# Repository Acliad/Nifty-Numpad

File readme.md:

Nifty Numpad is a full sized numpad with an extra row and two extra columns of macro keys. It was created because I wanted a companion to my TKL keyboard for work. My main workflow involves heavy use of ECAD programs, so the design was tailored for that, but it is generic enough to be nice for many workflows! 

The main features are:
- Full sized numpad with row of macro/function keys on the top
- Two extra columns of macro keys
- Cherry MX style socketed switches
- Backlit keys
- 3D printable case (FDM or resin)

.png "Render of Nifty Numpad")

# Contents
- [Contents](#contents)
- [Building One](#building-one)
  - [1. PCB Assembly](#1-pcb-assembly)
  - [2. 3D Printed Case](#2-3d-printed-case)
  - [3. Switch Mounting Plate](#3-switch-mounting-plate)
  - [4. Switches/Keycaps](#4-switcheskeycaps)
  - [5. Software](#5-software)
- [TODO](#todo)
  - [Software](#software)
- [Changelog](#changelog)
  - [PCB](#pcb)
    - [Rev 1](#rev-1)
  - [Software](#software-1)
  - [Mechanical](#mechanical)

# Building One
All of the files needed to build this numpad are in this repo (with software as a submodule and in the main QMK repo). The total BOM cost will be somewhere around $65-$85 shipped, but depends heavily on where and how you source things like switches, keycaps, plate, etc. For example, I bought 120x switches, but if you could get 33 switches for cheaper, you might save ~$10. 

## 1. PCB Assembly
The most difficult part of the build is soldering the RP2040 (microcontroller used) and associated components. It is highly recommended that you have the PCBs assembled. The files are in this repo for getting the PCB assembled through JLC PCB. You may save some money by soldering some of the components yourself (especially the sockets and LEDs). However, if you just love to solder this can be done with a stencil and plenty of time. I should know 🥲

You can choose to omit the LEDs if you're not into that sort of thing. It'll save you a few bucks. 

Parts marked as (DNF) in the BOM are not meant to be populated. If you want easy debugging for software development, you can populate R103, SW101, and SW102.

To have the PCB assembled:
1. Upload the gerber files from PCB/Main PCB/production/Nifty_Numpad.zip to JLC PCB.
2. Check the PCB Assembly toggle on the JLC PCB order page.
   1. Choose the PCBA Type. If you want JLC to solder the LEDs and sockets for you, you need to choose Standard. Otherwise, choose economy. Economy is a bit cheaper.
3. On the PCB Assembly page, you will need to upload the bom.csv and positions.csv file from PCB/Main PCB/production/
4. On the Components Placements page, make sure all of the ICs are orientated correctly. They usually aren't by default since JLC's library orientation is generally different from KiCad's.

To Solder the PCB assembly yourself:
1. Order PCBs (I use JLC, you can use whomever you like).
2. Order a stencil (you can usually do this at the same time as the PCB).
3. Order parts (I have DigiKey PNs in the electrical BOM, but again feel free to substitute)
   - The switch sockets are not available on DigiKey. [I bought mine on Amazon](https://www.amazon.com/dp/B0BVH6M5FP?psc=1&ref=ppx_yo2ov_dt_b_product_details), but you can source them from most keyboard suppliers.
   - The LEDs come in packs of 10. You can get them from DigiKey or Adafruit, but note if you upload the BOM directly to DigiKey it will put in a quantity of 33, which is actually 330.
4. Solder it!
    - I recommend a reflow oven, but a hot air station or hot plate works too.

## 2. 3D Printed Case
This case was initially designed to be 3D printed on a resin printer, but it actually prints best on an FDM printer. There are not special instructions here. You can either print the case yourself or have it printed using a service. JLC offers printing of many varieties. This might be a good choice if you're already ordering the PCB from them.

All the screw holes are designed to be tapped by a self-tapping screw. The BOM has some recommendations for some plastic-threading screws. 

I have added a "[shadow line](https://www.youtube.com/watch?v=8dhFhU7Nl_0)" to the case outline. There's a top-case print option with and without this line. I think it helps the look a bit for FDM prints, but it's up to you. 

It helps the sound profile considerably to fill up the case with some kind of dampening material. You could use foam or pour castable silicone into the case (I used [this one](https://www.amazon.com/gp/product/B07V5FFPWC/ref=ppx_yo_dt_b_search_asin_title?ie=UTF8&psc=1)). You can (and probably should) pour the silicone directly into the case. However, I've also included a mold for this in the Mechanical folder.

## 3. Switch Mounting Plate
I used [plate-mount](https://switchandclick.com/plate-mounted-vs-pcb-mounted-keyboard/) switches on this design. You can either make your own plate or have one made for you. There's a model of the plate as well as a DXF file in the Mechanical folder. Here is some information about some options:

1. Order a plate out of FR-4 when you order the PCB
   - This is a good option if you're already ordering the PCB from JLC. You can order the plate at the same time and save on shipping. 
   - This plate is quite rigid and I've found it to work well.
2. Order or make a custom plate out of your preferred material.
    - If you have a laser cutter or CNC, you can use the DXF or step file to make a plate out of whatever material you like! Many people use plexilgass, but you could use wood or metal. 
3. Use the provided 3D model of the plate to 3D print a plate.
   - The plate works, but it's quite flimsy and makes taking all the switches off the PCB tedious

Whatever you choose to do, you should find appropriate files in the Mechanical folder.

## 4. Switches/Keycaps
The fun part! Choose your favorite Cherry MX compatible switches and pop them in. If you're using LEDs, make sure you get switches with a clear top. 

I found it difficult to source backlit keycaps that fit this build well. You might be better off using non-backlit keycaps. There are [some AliExpress sellers](https://www.aliexpress.us/item/3256801609324454.html?spm=a2g0o.order_list.order_list_main.18.27561802CbfaCa&gatewayAdapt=glo2usa) who will sell portions of a keyboard at a time so you can mix and match colors. This is what I ended up doing, but I couldn't find any in a uniform profile like XDA or DSA. If you find a good source of keycaps, please share! 

If you're feeling plush, I think the numpad + icono kits of [these keycaps](https://drop.com/buy/drop-biip-mt3-extended-custom-keycap-set?mode%5B0%5D=shop_open&mode%5B1%5D=shop_open&defaultSelectionIds=969832&utm_source=google&utm_medium=cpc&utm_campaign=14650997430&utm_term=126026139486&utm_content=545898905914&utm_keyword=&utm_placement=pla-1392002507270&utm_network=u%3Ac%3A%3A&utm_device=&gad=1&gclid=CjwKCAjwlJimBhAsEiwA1hrp5i-AwICvpmNDm80DELJZylLo96oIX7IjxFvtUybMUVPNlUNpxAKwlxoCEOMQAvD_BwE&gclsrc=aw.ds) would be really nice. 

You'll also need 3x 2u plate-mount stabilizers. You can source these from most keyboard part suppliers or Ali Express.

## 5. Software
I've used [QMK](https://qmk.fm) for this build. Theere are builds for the [VIA](https://www.caniusevia.com) GUI configurator, a basic default usage, and an example for how to use the "fancy" RGB Idle mode and some tap-dance features. VIA is probably the easiest way to configure the keymap since you can configure it over a GUI, but if you're comfortable with QMK, you can do some cool customizations.

The Nifty Numpad has been merged into the main QMK repo, which you can find [here](https://github.com/qmk/qmk_firmware). My personal fork for developing the keyboard software is a submodule of this repo. You can find it [here](https://github.com/Acliad/qmk_firmware).

QMK and the build/flash process is pretty well document, so I'll leave that to the QMK community. If you have specific issues with the Nifty Numpad, feel free to message me. 

# TODO
## Software
- ~Implement VIAL for GUI remapping of buttons~
- ~Add other keymaps (an actual default and rename current to Cadence is a good start)~
- Create visual legend for RGB settings layer

# Changelog
## PCB
### Rev 1
- Changed footprint for W25Q40CLSNIG from wide to narrow footprint to match DigiKey PN
- Changed standoff holes to 6.0mm (from 4.6mm)
- Update LED footprint
- Add WASD graphic

## Software
- Added additional keymaps: default, VIA, and example. Old default moved to "Cadence" keymap
- Cleaned up code and file structure to align with QMK standards

## Mechanical
- Updated plate to use pan head screws
- Added clearance to top piece for pan head plate mount screws
- Moved "Designed By" tag to inside numpad
- Added a silicone sound dampening mold
- Added a "[shadow line](https://www.youtube.com/watch?v=8dhFhU7Nl_0)" model

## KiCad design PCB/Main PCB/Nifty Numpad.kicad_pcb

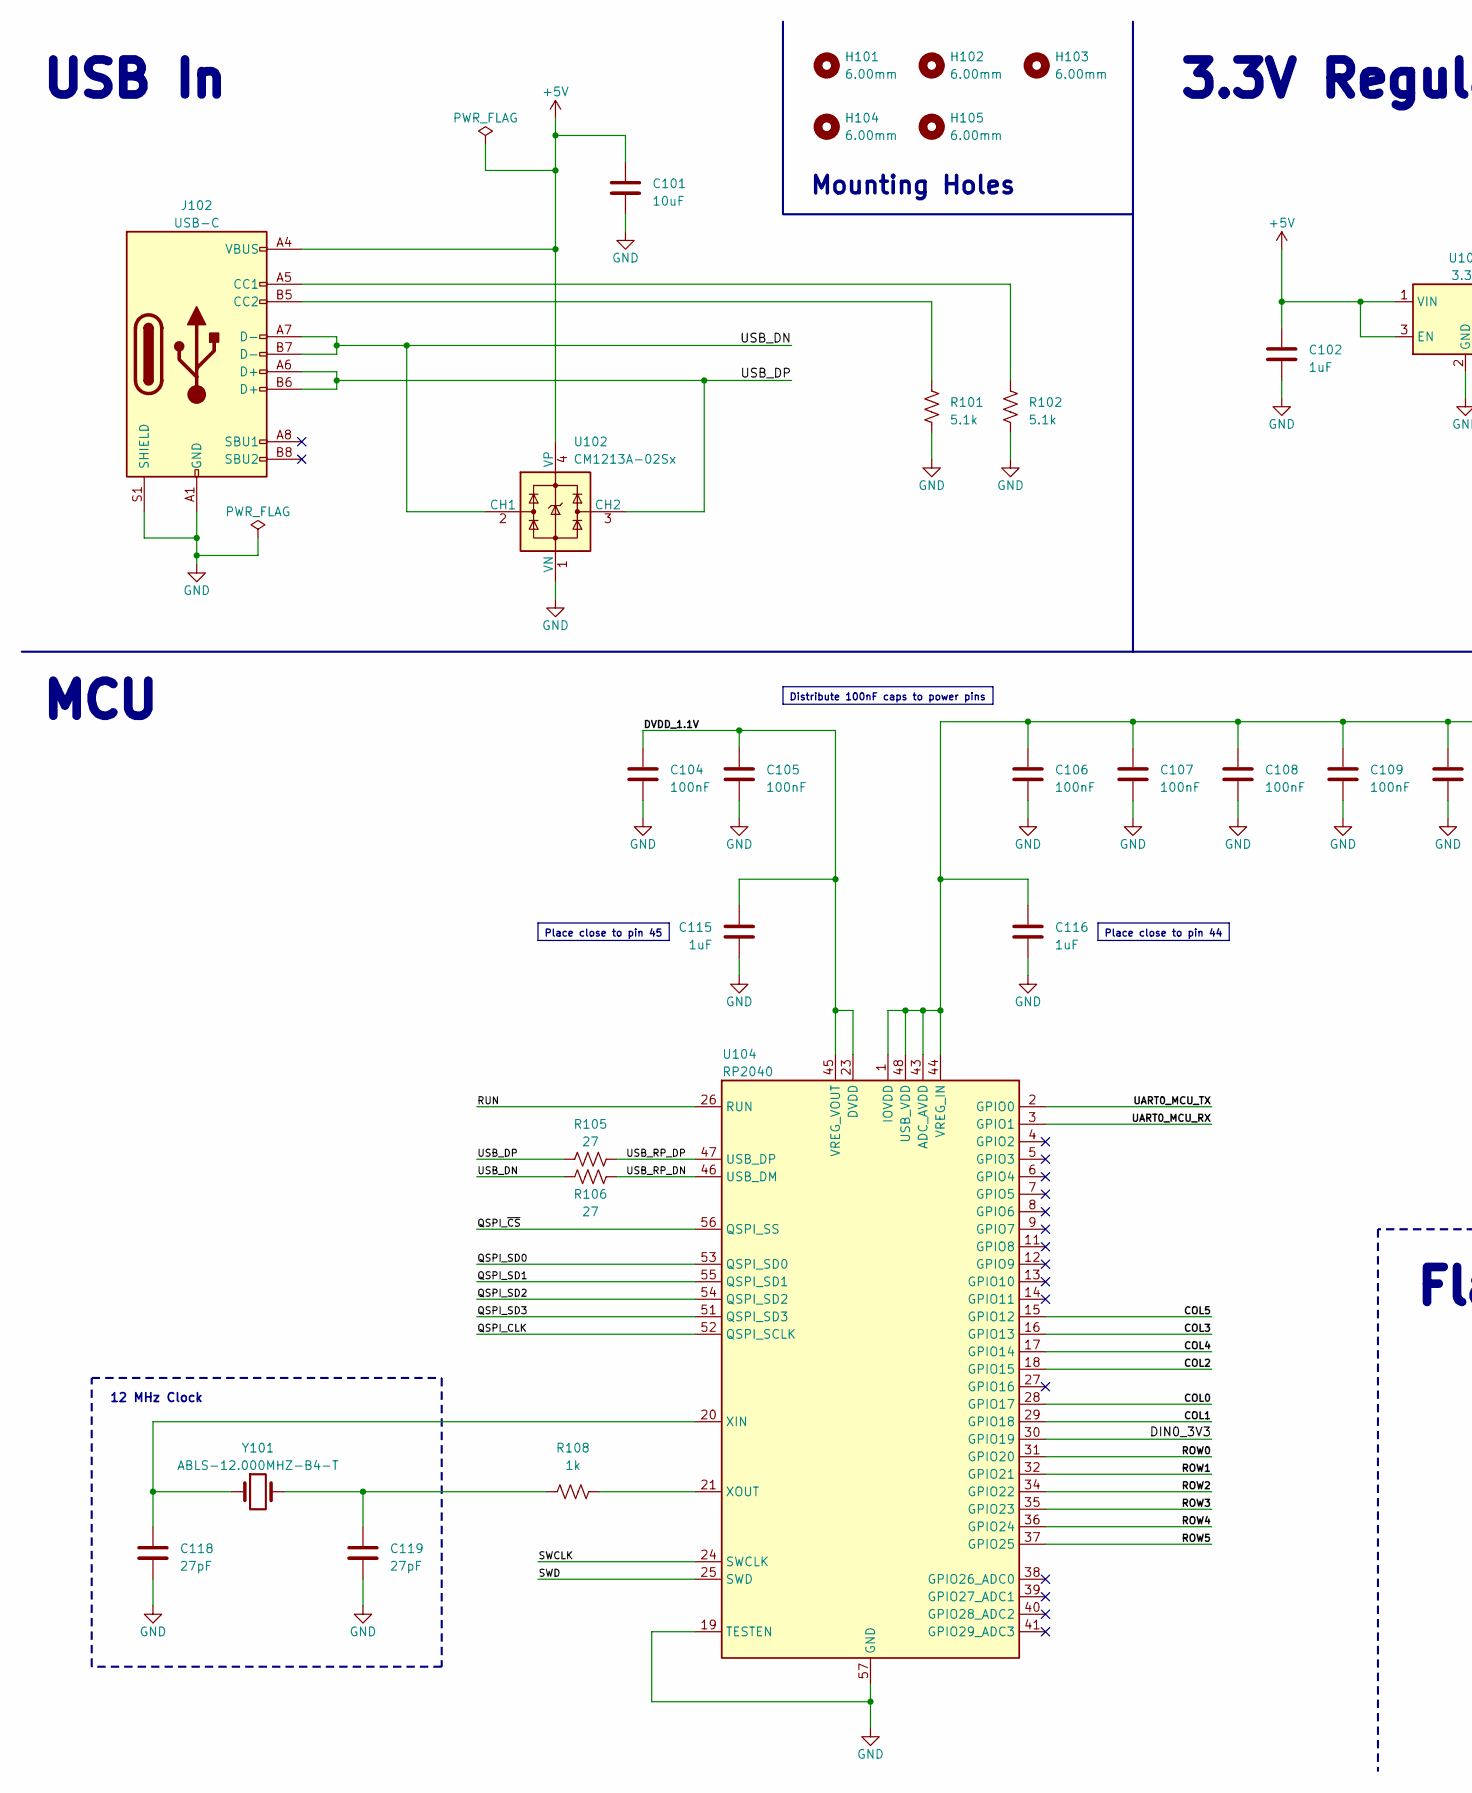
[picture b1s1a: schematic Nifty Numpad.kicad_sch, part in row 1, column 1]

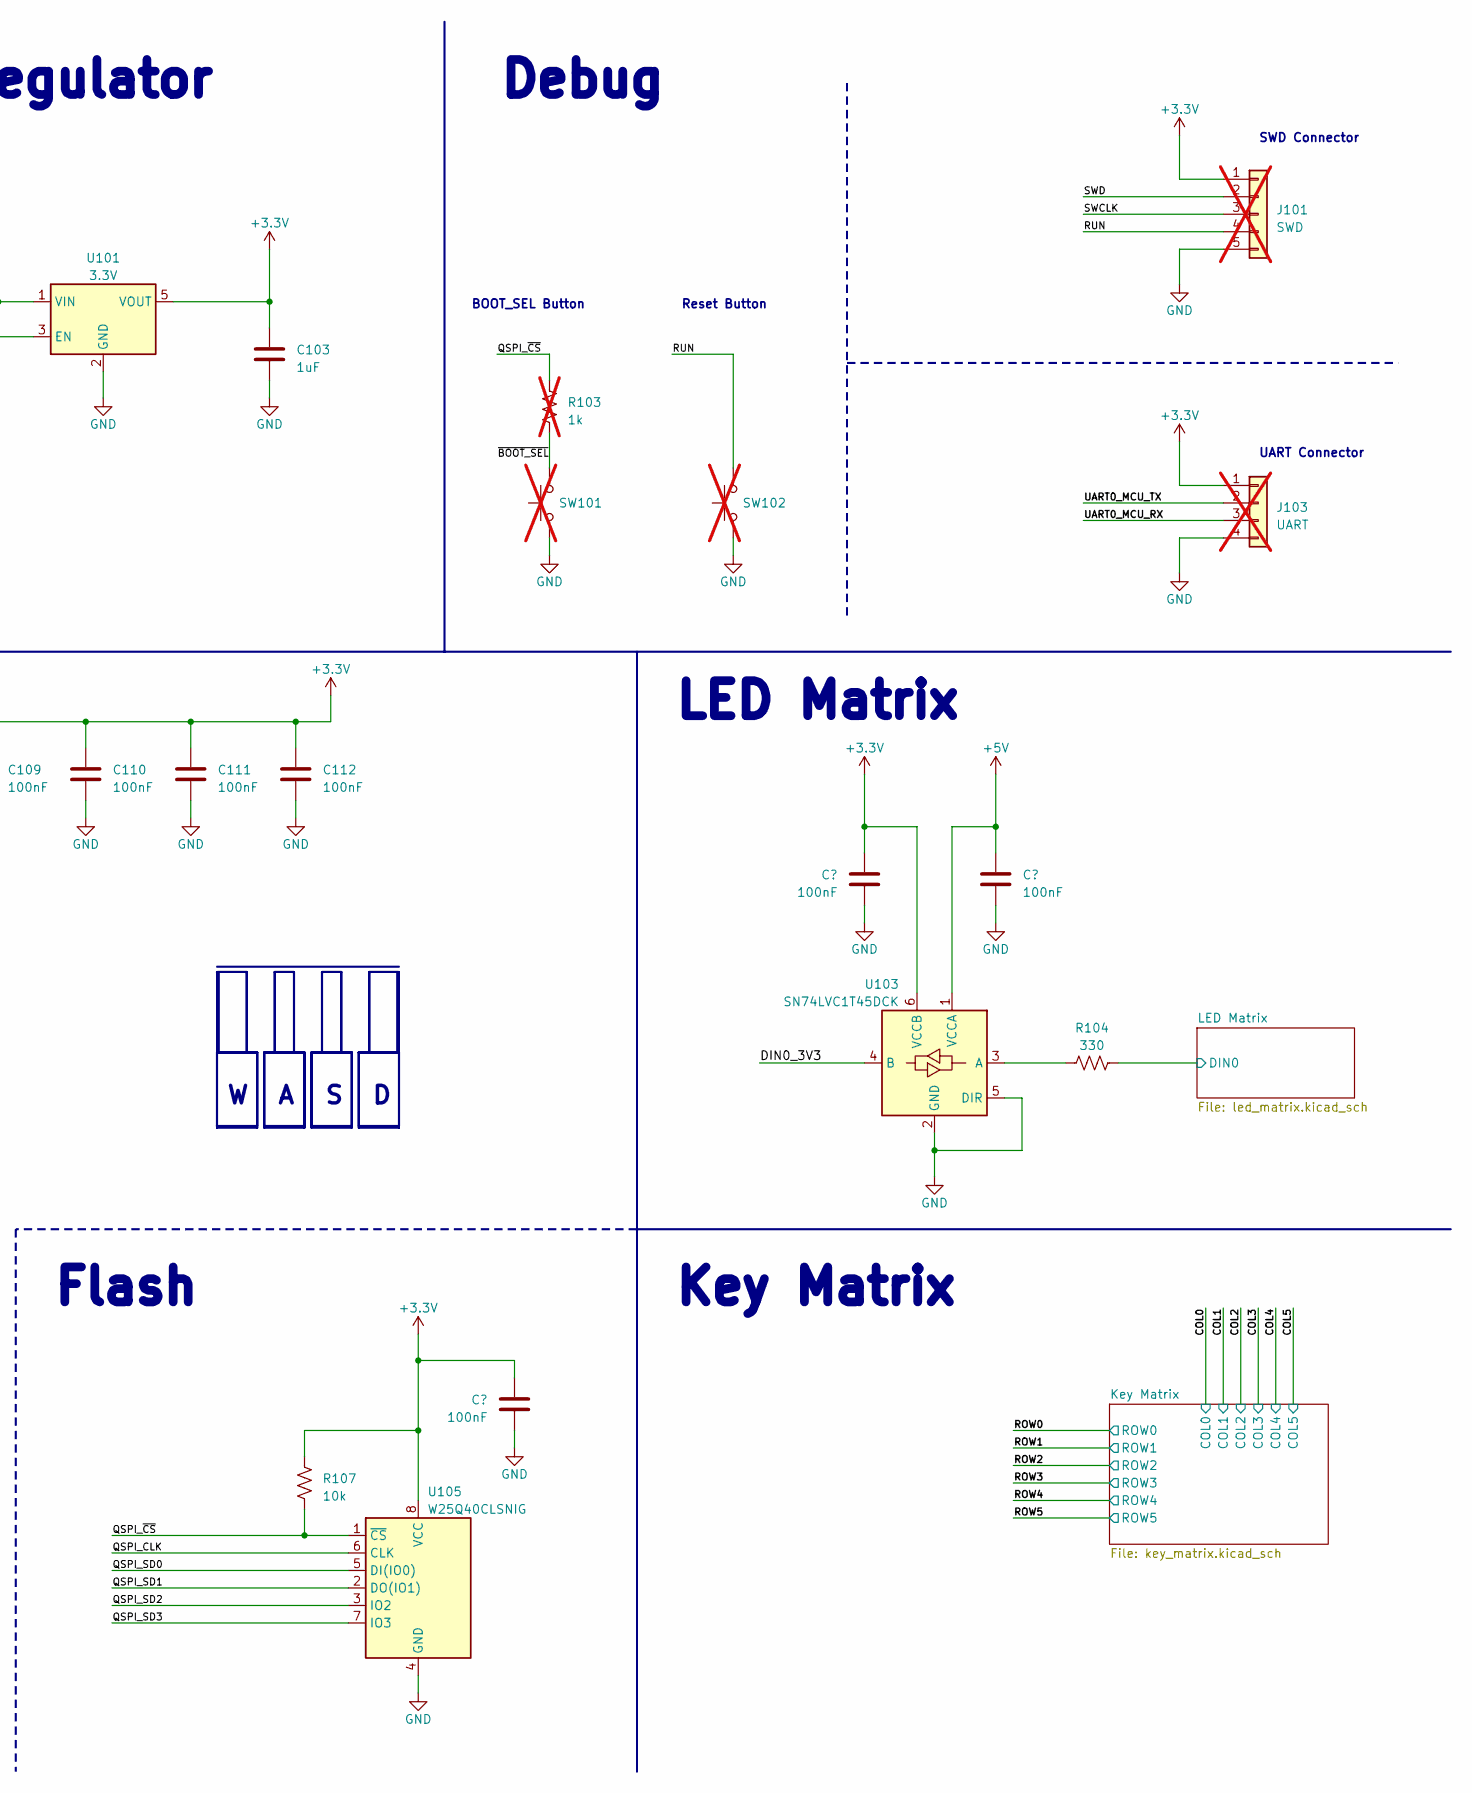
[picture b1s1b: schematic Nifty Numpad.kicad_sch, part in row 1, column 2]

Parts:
C101: 10uF; C_0603_1608Metric; DigiKey PN 490-10475-1-ND
C102, C103, C115, C116: 1uF; C_0603_1608Metric; DigiKey PN 1276-6524-1-ND
C104, C105, C106, C107, C108, C109, C110, C111, C112, C113, C114, C117: 100nF; C_0603_1608Metric; DigiKey PN 1276-1006-1-ND
C118, C119: 27pF; C_0603_1608Metric; DigiKey PN 1276-2247-1-ND
H101, H102, H103, H104, H105: 6.00mm; MountingHole_6.0mm_ReducedCourtyard
J101: SWD; PinHeader_1x05_P2.54mm_Vertical; DigiKey PN 2057-PH1-05-UA-ND; not fitted
J102: USB-C; USB_C_Receptacle_GCT_USB4105-GF-A-060; DigiKey PN 2073-USB4105-GF-A-060CT-ND
J103: UART; PinHeader_1x04_P2.54mm_Vertical; DigiKey PN 2057-PH1-04-UA-ND; not fitted
R101, R102: 5.1k; R_0603_1608Metric; DigiKey PN CR0603-FX-5101ELFCT-ND
R103: 1k; R_0603_1608Metric; DigiKey PN RNCP0603FTD1K00CT-ND; not fitted
R104: 330; R_0603_1608Metric; DigiKey PN CR0603-FX-3300ELFCT-ND
R105, R106: 27; R_0603_1608Metric; DigiKey PN CR0603-FX-27R0ELFCT-ND
R107: 10k; R_0603_1608Metric; DigiKey PN RNCP0603FTD1K00CT-ND
R108: 1k; R_0603_1608Metric; DigiKey PN RNCP0603FTD1K00CT-ND
SW101, SW102: PTS636 SL43 SMTR LFS; SW-PUSH-6x3.5mm_CK-PTS636SL43x_HandSolder; DigiKey PN CKN12309-1-ND; not fitted
U101: 3.3V; SOT-353_SC-70-5; DigiKey PN 576-3215-1-ND
U102: CM1213A−02Sx; SOT-143; DigiKey PN CM1213A-02SROSCT-ND
U103: SN74LVC1T45DCK; SOT-363_SC-70-6; DigiKey PN 31-74LVC1T45DW-7CT-ND
U104: RP2040; QFN-56-1EP_7x7mm_P0.4mm_EP3.2x3.2mm; DigiKey PN 2648-SC0914(13)CT-ND
U105: W25Q40CLSNIG; SOIC-8_3.9x4.9mm_P1.27mm; DigiKey PN W25Q40CLSNIG-ND
Y101: ABLS-12.000MHZ-B4-T; Crystal_SMD_HC49-SD; DigiKey PN 535-10218-1-ND

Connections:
+3.3V: C103.1, C106.1, C107.1, C108.1, C109.1, C110.1, C111.1, C112.1, C113.1, C116.1, C117.1, J101.1, J103.1, R107.1, U101.5 (VOUT), U103.6 (VCCB), U104.1 (IOVDD), U104.10 (IOVDD), U104.22 (IOVDD), U104.33 (IOVDD), U104.42 (IOVDD), U104.43 (ADC_AVDD), U104.44 (VREG_IN), U104.48 (USB_VDD), U104.49 (IOVDD), U105.8 (VCC)
+5V: C101.1, C102.1, C114.1, J102.A4 (VBUS), J102.A9 (VBUS), J102.B4 (VBUS), J102.B9 (VBUS), U101.1 (VIN), U101.3 (EN), U102.4 (VP), U103.1 (VCCA); also elsewhere on the board
/COL0: U104.28 (GPIO17); also elsewhere on the board
/COL1: U104.29 (GPIO18); also elsewhere on the board
/COL2: U104.18 (GPIO15); also elsewhere on the board
/COL3: U104.16 (GPIO13); also elsewhere on the board
/COL4: U104.17 (GPIO14); also elsewhere on the board
/COL5: U104.15 (GPIO12); also elsewhere on the board
/DIN0_3V3: U103.4 (B), U104.30 (GPIO19)
/DVDD_1.1V: C104.1, C105.1, C115.1, U104.23 (DVDD), U104.45 (VREG_VOUT), U104.50 (DVDD)
/LED Matrix/DIN0: R104.2; also elsewhere on the board
/QSPI_CLK: U104.52 (QSPI_SCLK), U105.6 (CLK)
/QSPI_SD0: U104.53 (QSPI_SD0), U105.5 (DI(IO0))
/QSPI_SD1: U104.55 (QSPI_SD1), U105.2 (DO(IO1))
/QSPI_SD2: U104.54 (QSPI_SD2), U105.3 (IO2)
/QSPI_SD3: U104.51 (QSPI_SD3), U105.7 (IO3)
/QSPI_~CS: R103.2, R107.2, U104.56 (QSPI_SS), U105.1 (~CS)
/ROW0: U104.31 (GPIO20); also elsewhere on the board
/ROW1: U104.32 (GPIO21); also elsewhere on the board
/ROW2: U104.34 (GPIO22); also elsewhere on the board
/ROW3: U104.35 (GPIO23); also elsewhere on the board
/ROW4: U104.36 (GPIO24); also elsewhere on the board
/ROW5: U104.37 (GPIO25); also elsewhere on the board
/RUN: J101.4, SW102.2, U104.26 (RUN)
/SWCLK: J101.3, U104.24 (SWCLK)
/SWD: J101.2, U104.25 (SWD)
/UART0_MCU_RX: J103.3, U104.3 (GPIO1)
/UART0_MCU_TX: J103.2, U104.2 (GPIO0)
/USB_DN: J102.A7 (D-), J102.B7 (D-), R106.1, U102.2 (CH1)
/USB_DP: J102.A6 (D+), J102.B6 (D+), R105.1, U102.3 (CH2)
/USB_RP_DN: R106.2, U104.46 (USB_DM)
/USB_RP_DP: R105.2, U104.47 (USB_DP)
/~BOOT_SEL: R103.1, SW101.2
GND: C101.2, C102.2, C103.2, C104.2, C105.2, C106.2, C107.2, C108.2, C109.2, C110.2, C111.2, C112.2, C113.2, C114.2, C115.2, C116.2, C117.2, C118.2, C119.2, J101.5, J102.A1 (GND), J102.A12 (GND), J102.B1 (GND), J102.B12 (GND), J102.S1 (SHIELD), J103.4, R101.2, R102.2, SW101.1, SW102.1, U101.2 (GND), U102.1 (VN), U103.2 (GND), U103.5 (DIR), U104.19 (TESTEN), U104.57 (GND), U105.4 (GND); also elsewhere on the board
unnamed: C119.1, R108.1, Y101.2
unnamed: J102.A5 (CC1), R102.1
unnamed: J102.B5 (CC2), R101.1
unnamed: R104.1, U103.3 (A)
unnamed: C118.1, U104.20 (XIN), Y101.1
unnamed: R108.2, U104.21 (XOUT)

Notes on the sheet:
Place close to pin 45
Distribute 100nF caps to power pins
Place close to pin 44
USB In
UART Connector
Debug
12 MHz Clock
Flash
SWD Connector
MCU
BOOT_SEL Button
Mounting Holes
Key Matrix
LED Matrix
Reset Button
3.3V Regulator

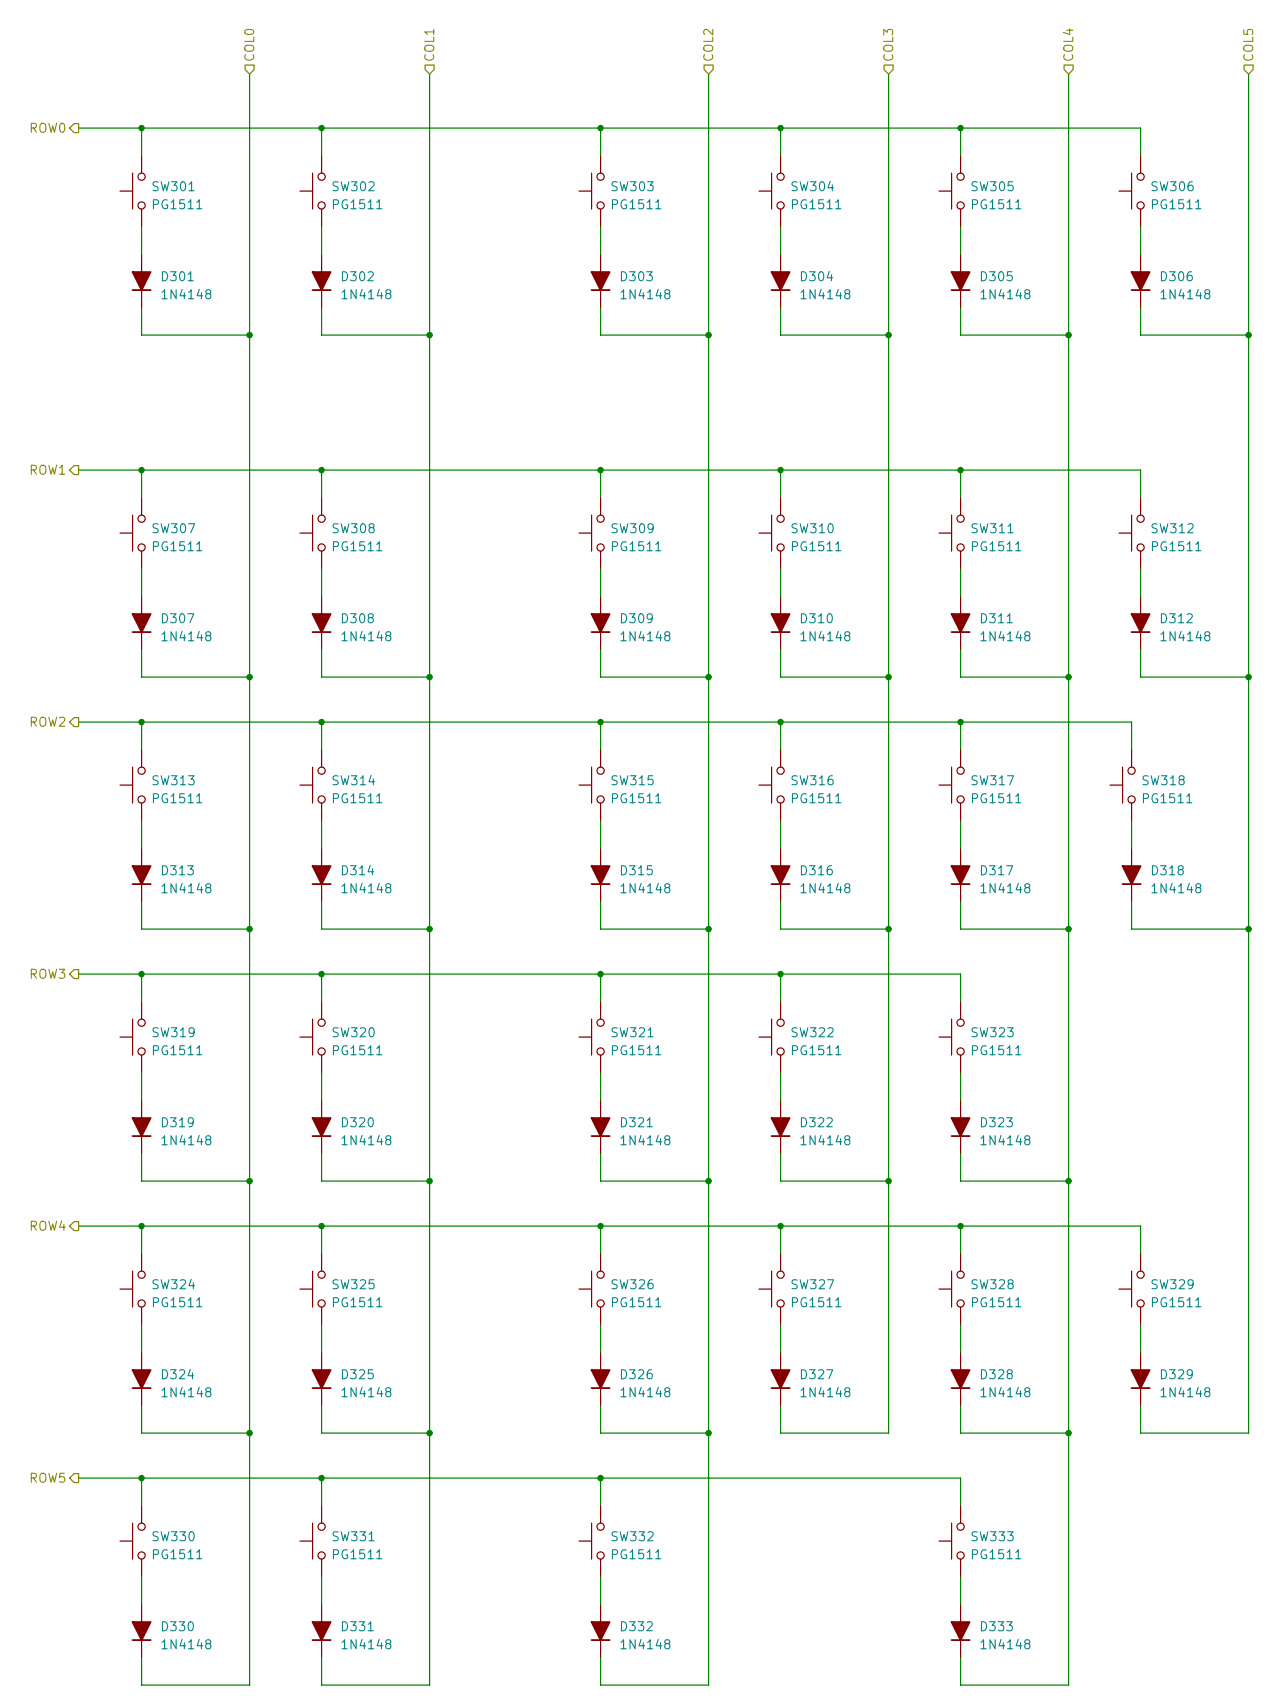
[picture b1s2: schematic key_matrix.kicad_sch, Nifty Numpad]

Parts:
D301, D302, D303, D304, D305, D306, D307, D308, D309, D310, D311, D312, D313, D314, D315, D316, D317, D318, D319, D320, D321, D322, D323, D324, D325, D326, D327, D328, D329, D330, D331, D332, D333: 1N4148; D_SOD-123; DigiKey PN 4530-1N4148WCT-ND
SW301, SW302, SW303, SW304, SW305, SW306, SW307, SW308, SW309, SW310, SW311, SW312, SW313, SW314, SW315, SW316, SW317, SW319, SW320, SW321, SW322, SW323, SW324, SW325, SW326, SW327, SW328, SW330, SW331, SW333: PG1511; SW_Hotswap_Kailh_MX_1.00u; LCSC C5156480
SW318, SW329: PG1511; SW_Hotswap_Kailh_MX_2.00u_90deg; LCSC C5156480
SW332: PG1511; SW_Hotswap_Kailh_MX_2.00u; LCSC C5156480

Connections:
/COL0: D301.1 (K), D307.1 (K), D313.1 (K), D319.1 (K), D324.1 (K), D330.1 (K); also elsewhere on the board
/COL1: D302.1 (K), D308.1 (K), D314.1 (K), D320.1 (K), D325.1 (K), D331.1 (K); also elsewhere on the board
/COL2: D303.1 (K), D309.1 (K), D315.1 (K), D321.1 (K), D326.1 (K), D332.1 (K); also elsewhere on the board
/COL3: D304.1 (K), D310.1 (K), D316.1 (K), D322.1 (K), D327.1 (K); also elsewhere on the board
/COL4: D305.1 (K), D311.1 (K), D317.1 (K), D323.1 (K), D328.1 (K), D333.1 (K); also elsewhere on the board
/COL5: D306.1 (K), D312.1 (K), D318.1 (K), D329.1 (K); also elsewhere on the board
/ROW0: SW301.2, SW302.2, SW303.2, SW304.2, SW305.2, SW306.2; also elsewhere on the board
/ROW1: SW307.2, SW308.2, SW309.2, SW310.2, SW311.2, SW312.2; also elsewhere on the board
/ROW2: SW313.2, SW314.2, SW315.2, SW316.2, SW317.2, SW318.2; also elsewhere on the board
/ROW3: SW319.2, SW320.2, SW321.2, SW322.2, SW323.2; also elsewhere on the board
/ROW4: SW324.2, SW325.2, SW326.2, SW327.2, SW328.2, SW329.2; also elsewhere on the board
/ROW5: SW330.2, SW331.2, SW332.2, SW333.2; also elsewhere on the board
unnamed: D301.2 (A), SW301.1
unnamed: D302.2 (A), SW302.1
unnamed: D303.2 (A), SW303.1
unnamed: D304.2 (A), SW304.1
unnamed: D305.2 (A), SW305.1
unnamed: D306.2 (A), SW306.1
unnamed: D307.2 (A), SW307.1
unnamed: D308.2 (A), SW308.1
unnamed: D309.2 (A), SW309.1
unnamed: D310.2 (A), SW310.1
unnamed: D311.2 (A), SW311.1
unnamed: D312.2 (A), SW312.1
unnamed: D313.2 (A), SW313.1
unnamed: D314.2 (A), SW314.1
unnamed: D315.2 (A), SW315.1
unnamed: D316.2 (A), SW316.1
unnamed: D317.2 (A), SW317.1
unnamed: D318.2 (A), SW318.1
unnamed: D319.2 (A), SW319.1
unnamed: D320.2 (A), SW320.1
unnamed: D321.2 (A), SW321.1
unnamed: D322.2 (A), SW322.1
unnamed: D323.2 (A), SW323.1
unnamed: D324.2 (A), SW324.1
unnamed: D325.2 (A), SW325.1
unnamed: D326.2 (A), SW326.1
unnamed: D327.2 (A), SW327.1
unnamed: D328.2 (A), SW328.1
unnamed: D329.2 (A), SW329.1
unnamed: D330.2 (A), SW330.1
unnamed: D331.2 (A), SW331.1
unnamed: D332.2 (A), SW332.1
unnamed: D333.2 (A), SW333.1

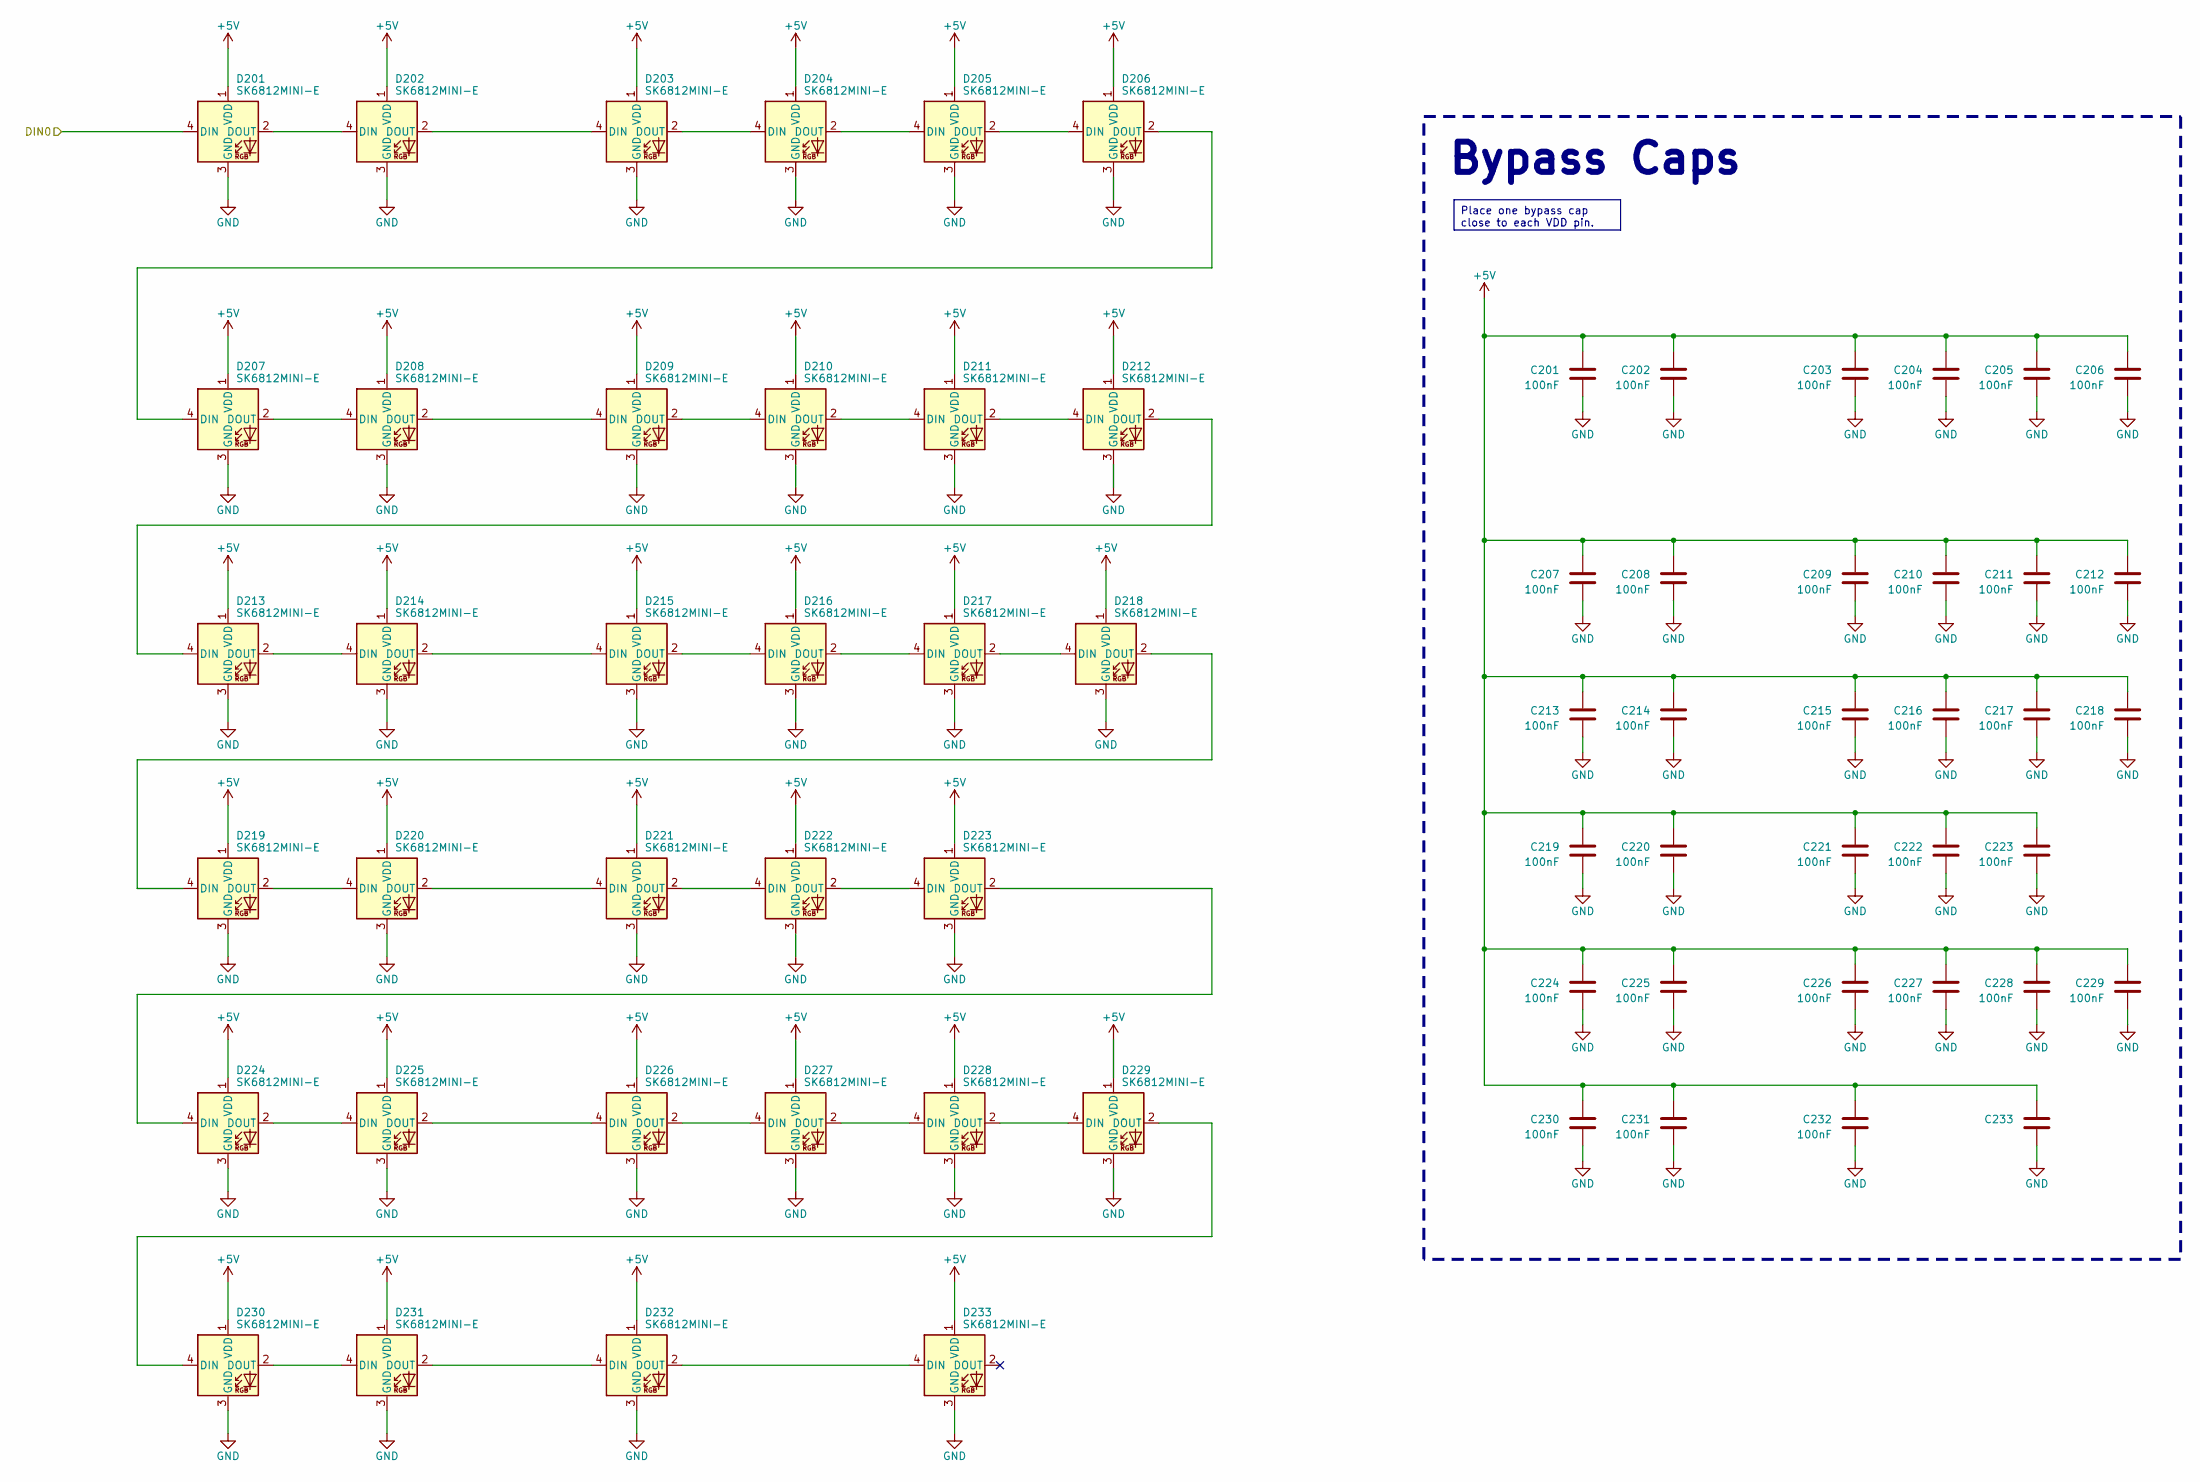
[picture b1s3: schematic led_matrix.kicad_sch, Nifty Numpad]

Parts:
C201, C202, C203, C204, C205, C206, C207, C208, C209, C210, C211, C212, C213, C214, C215, C216, C217, C218, C219, C220, C221, C222, C223, C224, C225, C226, C227, C228, C229, C230, C231, C232, C233: 100nF; C_0603_1608Metric; DigiKey PN 1276-1006-1-ND
D201, D202, D203, D204, D205, D206, D207, D208, D209, D210, D211, D212, D213, D214, D215, D216, D217, D218, D219, D220, D221, D222, D223, D224, D225, D226, D227, D228, D229, D230, D231, D232, D233: SK6812MINI-E; LED_SK6812MINI-E_3.2x2.8mm; DigiKey PN 1528-4960-ND

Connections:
+5V: C201.1, C202.1, C203.1, C204.1, C205.1, C206.1, C207.1, C208.1, C209.1, C210.1, C211.1, C212.1, C213.1, C214.1, C215.1, C216.1, C217.1, C218.1, C219.1, C220.1, C221.1, C222.1, C223.1, C224.1, C225.1, C226.1, C227.1, C228.1, C229.1, C230.1, C231.1, C232.1, C233.1, D201.1 (VDD), D202.1 (VDD), D203.1 (VDD), D204.1 (VDD), D205.1 (VDD), D206.1 (VDD), D207.1 (VDD), D208.1 (VDD), D209.1 (VDD), D210.1 (VDD), D211.1 (VDD), D212.1 (VDD), D213.1 (VDD), D214.1 (VDD), D215.1 (VDD), D216.1 (VDD), D217.1 (VDD), D218.1 (VDD), D219.1 (VDD), D220.1 (VDD), D221.1 (VDD), D222.1 (VDD), D223.1 (VDD), D224.1 (VDD), D225.1 (VDD), D226.1 (VDD), D227.1 (VDD), D228.1 (VDD), D229.1 (VDD), D230.1 (VDD), D231.1 (VDD), D232.1 (VDD), D233.1 (VDD); also elsewhere on the board
/LED Matrix/DIN0: D201.4 (DIN); also elsewhere on the board
GND: C201.2, C202.2, C203.2, C204.2, C205.2, C206.2, C207.2, C208.2, C209.2, C210.2, C211.2, C212.2, C213.2, C214.2, C215.2, C216.2, C217.2, C218.2, C219.2, C220.2, C221.2, C222.2, C223.2, C224.2, C225.2, C226.2, C227.2, C228.2, C229.2, C230.2, C231.2, C232.2, C233.2, D201.3 (GND), D202.3 (GND), D203.3 (GND), D204.3 (GND), D205.3 (GND), D206.3 (GND), D207.3 (GND), D208.3 (GND), D209.3 (GND), D210.3 (GND), D211.3 (GND), D212.3 (GND), D213.3 (GND), D214.3 (GND), D215.3 (GND), D216.3 (GND), D217.3 (GND), D218.3 (GND), D219.3 (GND), D220.3 (GND), D221.3 (GND), D222.3 (GND), D223.3 (GND), D224.3 (GND), D225.3 (GND), D226.3 (GND), D227.3 (GND), D228.3 (GND), D229.3 (GND), D230.3 (GND), D231.3 (GND), D232.3 (GND), D233.3 (GND); also elsewhere on the board
unnamed: D201.2 (DOUT), D202.4 (DIN)
unnamed: D202.2 (DOUT), D203.4 (DIN)
unnamed: D203.2 (DOUT), D204.4 (DIN)
unnamed: D204.2 (DOUT), D205.4 (DIN)
unnamed: D205.2 (DOUT), D206.4 (DIN)
unnamed: D206.2 (DOUT), D207.4 (DIN)
unnamed: D207.2 (DOUT), D208.4 (DIN)
unnamed: D208.2 (DOUT), D209.4 (DIN)
unnamed: D209.2 (DOUT), D210.4 (DIN)
unnamed: D210.2 (DOUT), D211.4 (DIN)
unnamed: D211.2 (DOUT), D212.4 (DIN)
unnamed: D212.2 (DOUT), D213.4 (DIN)
unnamed: D213.2 (DOUT), D214.4 (DIN)
unnamed: D214.2 (DOUT), D215.4 (DIN)
unnamed: D215.2 (DOUT), D216.4 (DIN)
unnamed: D216.2 (DOUT), D217.4 (DIN)
unnamed: D217.2 (DOUT), D218.4 (DIN)
unnamed: D218.2 (DOUT), D219.4 (DIN)
unnamed: D219.2 (DOUT), D220.4 (DIN)
unnamed: D220.2 (DOUT), D221.4 (DIN)
unnamed: D221.2 (DOUT), D222.4 (DIN)
unnamed: D222.2 (DOUT), D223.4 (DIN)
unnamed: D223.2 (DOUT), D224.4 (DIN)
unnamed: D224.2 (DOUT), D225.4 (DIN)
unnamed: D225.2 (DOUT), D226.4 (DIN)
unnamed: D226.2 (DOUT), D227.4 (DIN)
unnamed: D227.2 (DOUT), D228.4 (DIN)
unnamed: D228.2 (DOUT), D229.4 (DIN)
unnamed: D229.2 (DOUT), D230.4 (DIN)
unnamed: D230.2 (DOUT), D231.4 (DIN)
unnamed: D231.2 (DOUT), D232.4 (DIN)
unnamed: D232.2 (DOUT), D233.4 (DIN)

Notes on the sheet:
Place one bypass cap close to each VDD pin.
Bypass Caps
